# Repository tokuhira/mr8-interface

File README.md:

# mr8-interface

KO PROPO製のプロポセットMC-8/MR-8にマルチプレクサ機能等を追加するプロジェクトです。

# Features

CMOSロジックICのマルチプレクサを利用してプロポからの操作と別系統からの操作を選択できます。
操作系統の切り替えはMC-8の操作スティック押下で行います。
CH-Eを押すと別系統の操作が有効になり、CH-Fを押すとプロポによる手動操作に戻ります。
別系統との電気信号は絶縁されているため、異なる電源系統のユニットとも接続できます。
おまけ機能で両系統のステアリングともにリバース信号も出力します。
おまけ機能でプロポ操作に対応するS.BUS信号も出力する予定ですが、プログラムは未実装です。

# Requirement

Adafruit QT Pyが別途必要です。

# Installation

このボードとAdafruit QT Pyは直接ハンダ付けします。
このボードとMR-8の接続については回路図を参照のうえ、ハーネスもしくは添付のミニ基板を使用してください。
このボードとRCシステム（スロットルに対応するESC、ならびにステアリングに対応するサーボ）の接続についても回路図を参照してください。
TAKACHI製のプラスチックケースTW4-2-5に格納することができます。
TAKACHI製のプラスチックケースSW-40にも格納することができますが、その場合はマウントホールのはみ出し部を切り落とす必要があります。

# Usage

各々方でご自由に応用していただけます。

# Note

可用性、安全性、その他いかなる性質も保証しません。
いかなる用法も、またのその結果も保証しません。

# Author

* @tokuhira (twitter)
* github.com/tokuhira

# License

BSD 3-Clause License

Copyright (c) 2020, tokuhira.net
All rights reserved.

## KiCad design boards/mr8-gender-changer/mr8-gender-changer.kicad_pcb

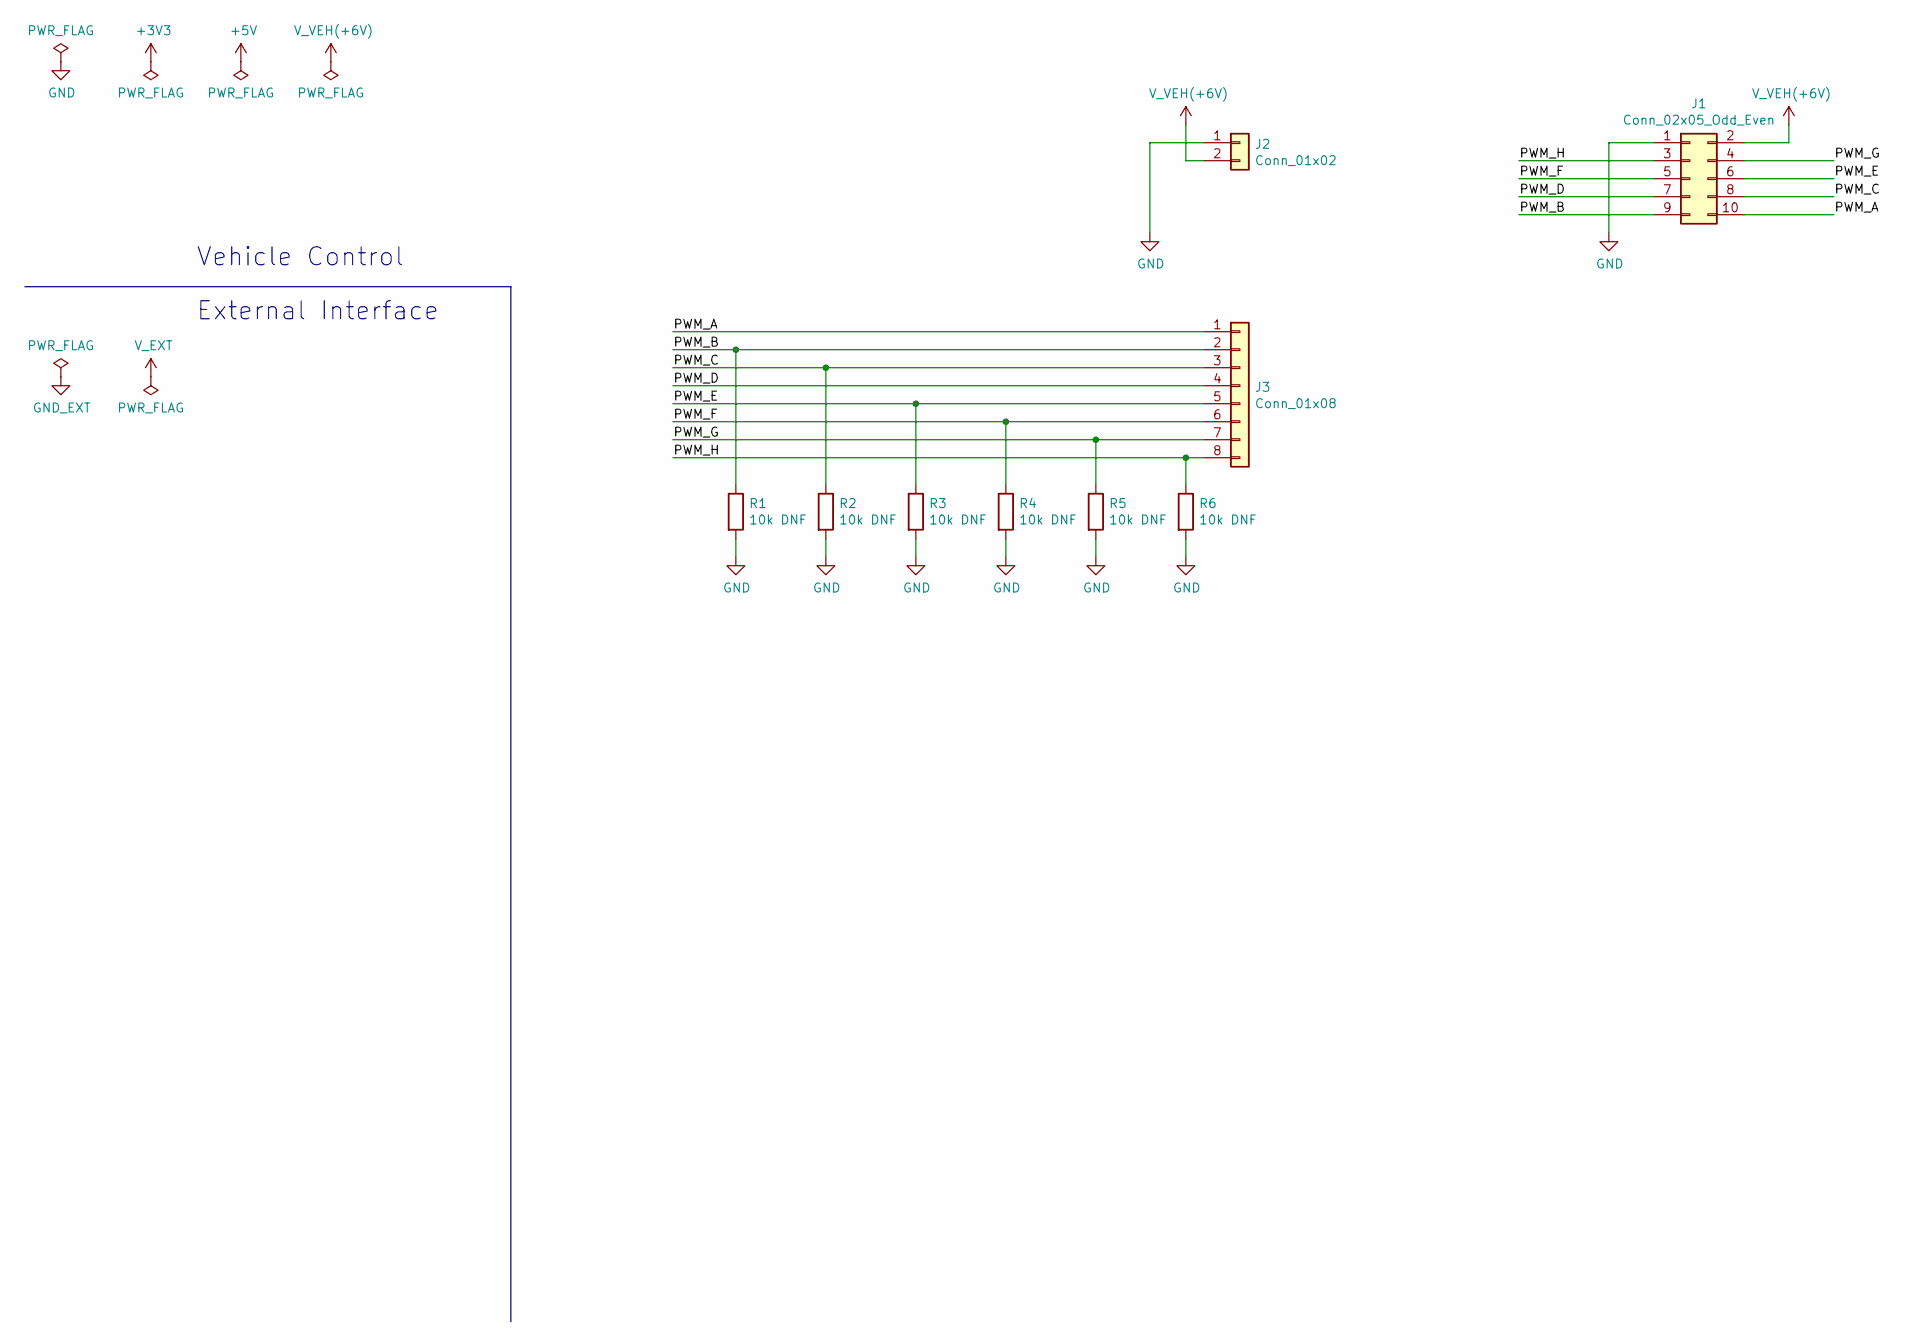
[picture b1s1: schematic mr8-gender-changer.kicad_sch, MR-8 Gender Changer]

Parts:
J1: Conn_02x05_Odd_Even; PinSocket_1x10_P2.54mm_Vertical
J2: Conn_01x02; PinSocket_1x02_P2.54mm_Vertical
J3: Conn_01x08; PinSocket_1x08_P2.54mm_Vertical
R1, R2, R3, R4, R5, R6: 10k DNF; R_0603_1608Metric_Pad0.98x0.95mm_HandSolder

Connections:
+V_VEH: J1.2, J2.2
/PWM_A: J1.10, J3.1
/PWM_B: J1.9, J3.2, R1.1
/PWM_C: J1.8, J3.3, R2.1
/PWM_D: J1.7, J3.4
/PWM_E: J1.6, J3.5, R3.1
/PWM_F: J1.5, J3.6, R4.1
/PWM_G: J1.4, J3.7, R5.1
/PWM_H: J1.3, J3.8, R6.1
GND: J1.1, J2.1, R1.2, R2.2, R3.2, R4.2, R5.2, R6.2

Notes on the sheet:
Vehicle Control
External Interface

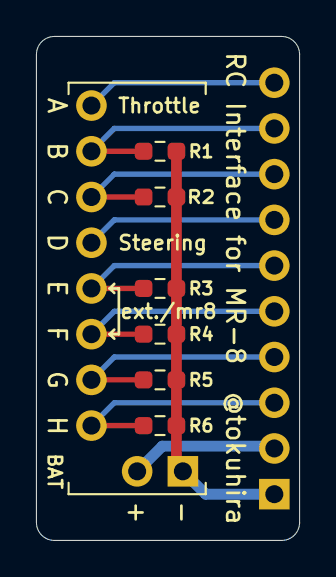
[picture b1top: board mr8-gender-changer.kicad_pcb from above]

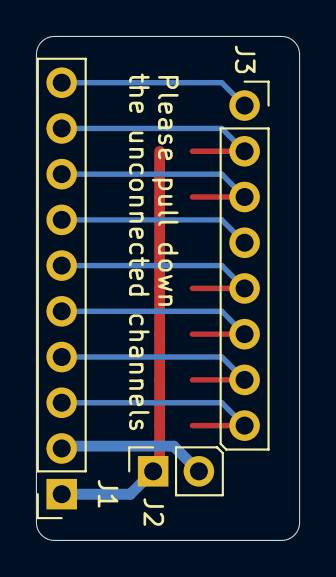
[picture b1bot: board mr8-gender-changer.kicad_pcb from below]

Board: 2 copper layers, 14.6 x 28.0 mm, 9 parts (3 on the bottom side), 10 nets.

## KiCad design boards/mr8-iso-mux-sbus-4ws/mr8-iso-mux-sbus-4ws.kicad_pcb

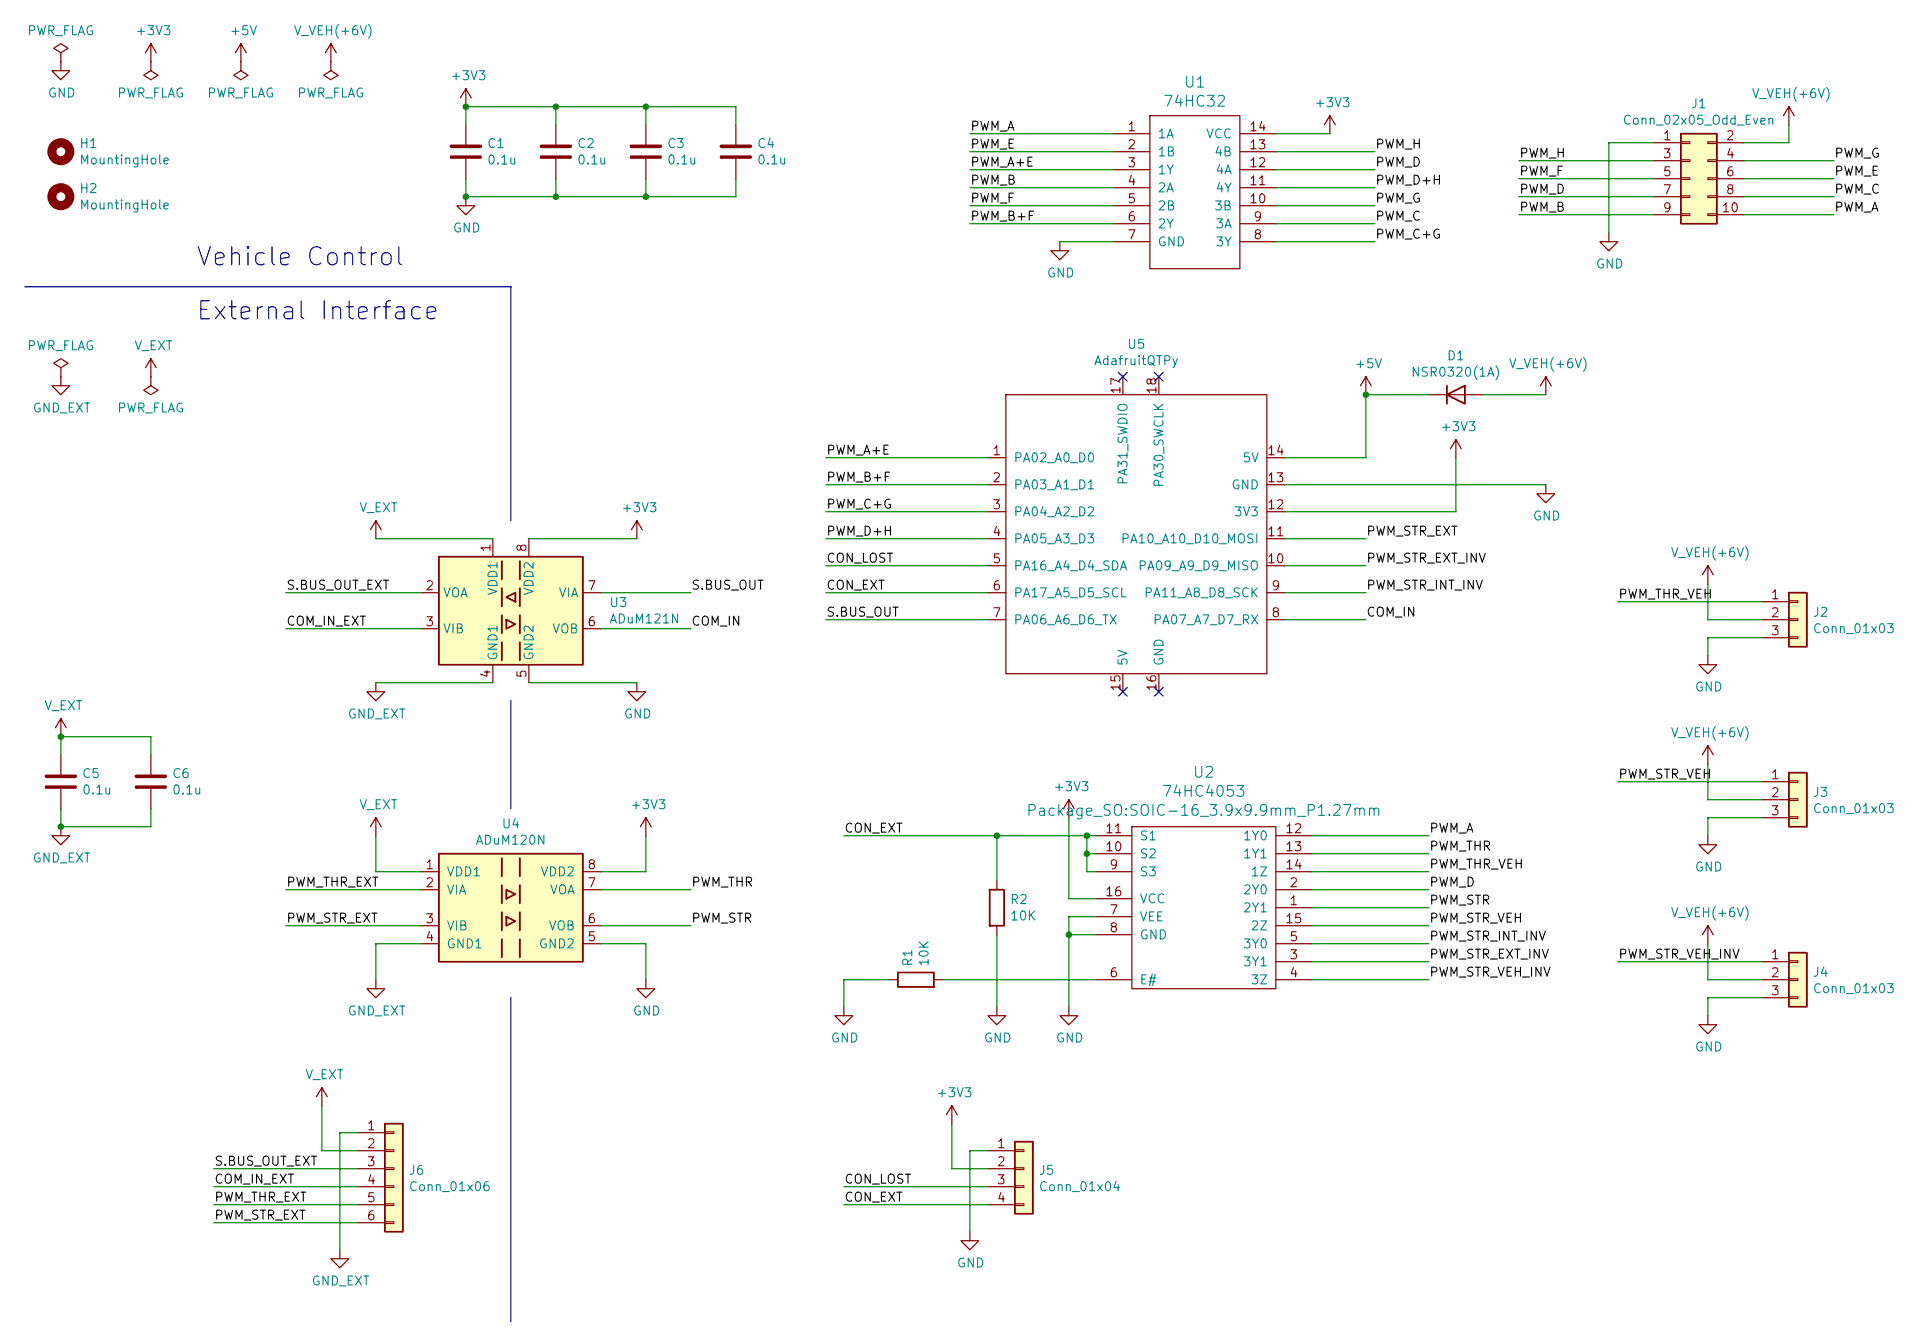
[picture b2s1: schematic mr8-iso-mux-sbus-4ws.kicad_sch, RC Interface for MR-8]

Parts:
C1, C2, C3, C4, C5, C6: 0.1u; C_0603_1608Metric_Pad1.08x0.95mm_HandSolder
D1: NSR0320(1A); D_SOD-323_HandSoldering
H1, H2: MountingHole; MountingHole_2.2mm_M2
J1: Conn_02x05_Odd_Even; PinHeader_1x10_P2.54mm_Vertical
J2, J3, J4: Conn_01x03; PinHeader_1x03_P2.54mm_Vertical
J5: Conn_01x04; PinHeader_1x04_P2.54mm_Vertical
J6: Conn_01x06; PinHeader_1x06_P2.54mm_Vertical
R1, R2: 10K; R_0603_1608Metric_Pad0.98x0.95mm_HandSolder
U1: 74HC32; SOIC-14_3.9x8.7mm_P1.27mm
U2: 74HC4053; SOIC-16_3.9x9.9mm_P1.27mm
U3: ADuM121N; SOIC-8_3.9x4.9mm_P1.27mm
U4: ADuM120N; SOIC-8_3.9x4.9mm_P1.27mm
U5: AdafruitQTPy; AdafruitQTPy-MOUDLE14P-2.54-21X17.8MM

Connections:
+3V3: C1.1, C2.1, C3.1, C4.1, J5.2, U1.14 (VCC), U2.16 (VCC), U3.8 (VDD2), U4.8 (VDD2), U5.12 (3V3)
+5V: D1.1 (K), U5.14 (5V)
+V_EXT: C5.1, C6.1, J6.2, U3.1 (VDD1), U4.1 (VDD1)
+V_VEH: D1.2 (A), J1.2, J2.2, J3.2, J4.2
/COM_IN: U3.6 (VOB), U5.8 (PA07_A7_D7_RX)
/COM_IN_EXT: J6.4, U3.3 (VIB)
/CON_EXT: J5.4, R2.1, U2.9 (S3), U2.10 (S2), U2.11 (S1), U5.6 (PA17_A5_D5_SCL)
/CON_LOST: J5.3, U5.5 (PA16_A4_D4_SDA)
/PWM_A: J1.10, U1.1 (1A), U2.12 (1Y0)
/PWM_A+E: U1.3 (1Y), U5.1 (PA02_A0_D0)
/PWM_B: J1.9, U1.4 (2A)
/PWM_B+F: U1.6 (2Y), U5.2 (PA03_A1_D1)
/PWM_C: J1.8, U1.9 (3A)
/PWM_C+G: U1.8 (3Y), U5.3 (PA04_A2_D2)
/PWM_D: J1.7, U1.12 (4A), U2.2 (2Y0)
/PWM_D+H: U1.11 (4Y), U5.4 (PA05_A3_D3)
/PWM_E: J1.6, U1.2 (1B)
/PWM_F: J1.5, U1.5 (2B)
/PWM_G: J1.4, U1.10 (3B)
/PWM_H: J1.3, U1.13 (4B)
/PWM_STR: U2.1 (2Y1), U4.6 (VOB)
/PWM_STR_EXT: J6.6, U4.3 (VIB), U5.11 (PA10_A10_D10_MOSI)
/PWM_STR_EXT_INV: U2.3 (3Y1), U5.10 (PA09_A9_D9_MISO)
/PWM_STR_INT_INV: U2.5 (3Y0), U5.9 (PA11_A8_D8_SCK)
/PWM_STR_VEH: J3.1, U2.15 (2Z)
/PWM_STR_VEH_INV: J4.1, U2.4 (3Z)
/PWM_THR: U2.13 (1Y1), U4.7 (VOA)
/PWM_THR_EXT: J6.5, U4.2 (VIA)
/PWM_THR_VEH: J2.1, U2.14 (1Z)
/S.BUS_OUT: U3.7 (VIA), U5.7 (PA06_A6_D6_TX)
/S.BUS_OUT_EXT: J6.3, U3.2 (VOA)
GND: C1.2, C2.2, C3.2, C4.2, J1.1, J2.3, J3.3, J4.3, J5.1, R1.1, R2.2, U1.7 (GND), U2.7 (VEE), U2.8 (GND), U3.5 (GND2), U4.5 (GND2), U5.13 (GND)
GND_EXT: C5.2, C6.2, J6.1, U3.4 (GND1), U4.4 (GND1)
unnamed: R1.2, U2.6 (E#)

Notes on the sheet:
Vehicle Control
External Interface

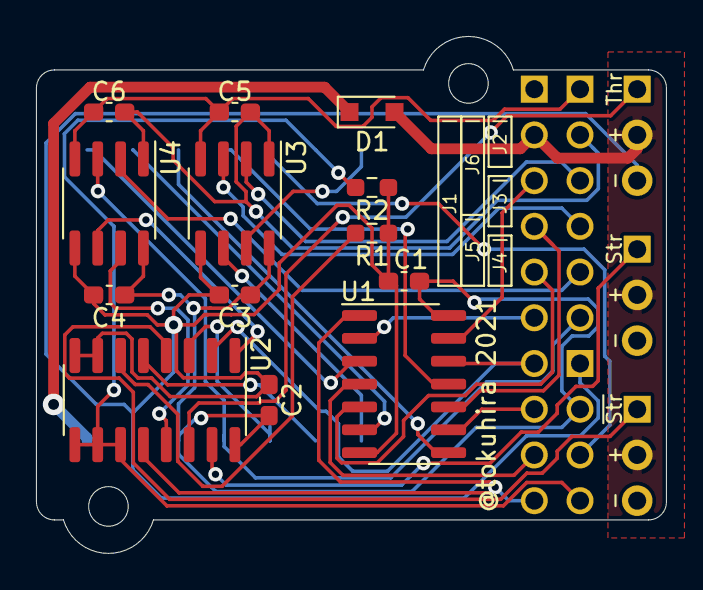
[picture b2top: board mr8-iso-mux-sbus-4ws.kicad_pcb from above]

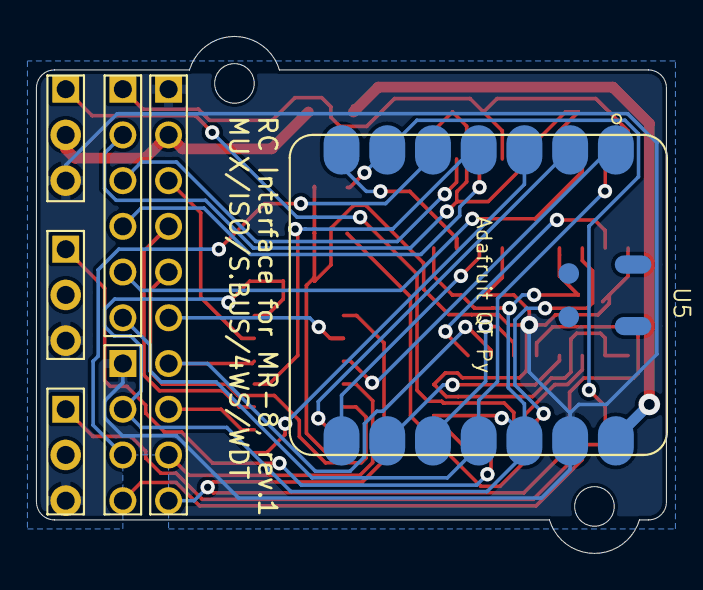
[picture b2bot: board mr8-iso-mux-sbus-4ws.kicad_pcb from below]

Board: 2 copper layers, 35.0 x 28.7 mm, 22 parts (7 on the bottom side), 34 nets.

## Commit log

2022-02-21 Create adruino and boards
    KiCad 5.1系の基板設計データおよびS.BUS未対応のプログラム
2023-03-05 KiCad 7
    Update file names and formats for KiCad 7.
2023-03-05 Update RC_Interface_for_MR-8.ino
    Add protection from unexpected interrupts on intialization.
2023-03-05 Update RC_Interface_for_MR-8.ino
    Typo.
